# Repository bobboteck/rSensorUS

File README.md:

rSensorUS
=========

rSensorUS is a board for control up to 8 HC-SR04 Ultrasonic ranging modules based on Microchip PIC 18F2620.

The board have two analog input and one I2C master port, theoretically will be used to connect a temperature and humidity sensors, with the purpose of compensate the measurements of the ultrasonic sensors.

the communication with master controller can take place via serial TTL or RS-485.

The power voltage is 5 Volt.

Software develop used
======================
Currently the electric schema and the PCB was designed with Eagle 6.4 version, by CADSoft

For the code currently used MPLAB X version 1.90 and XC8 version 1.20, by Microchip

Now
====
Actualy working on Branch "Communication" to implement the Serial communication and protocol to mange the message and command received from Master

More info
==========
You can see more info on project in the wiki section

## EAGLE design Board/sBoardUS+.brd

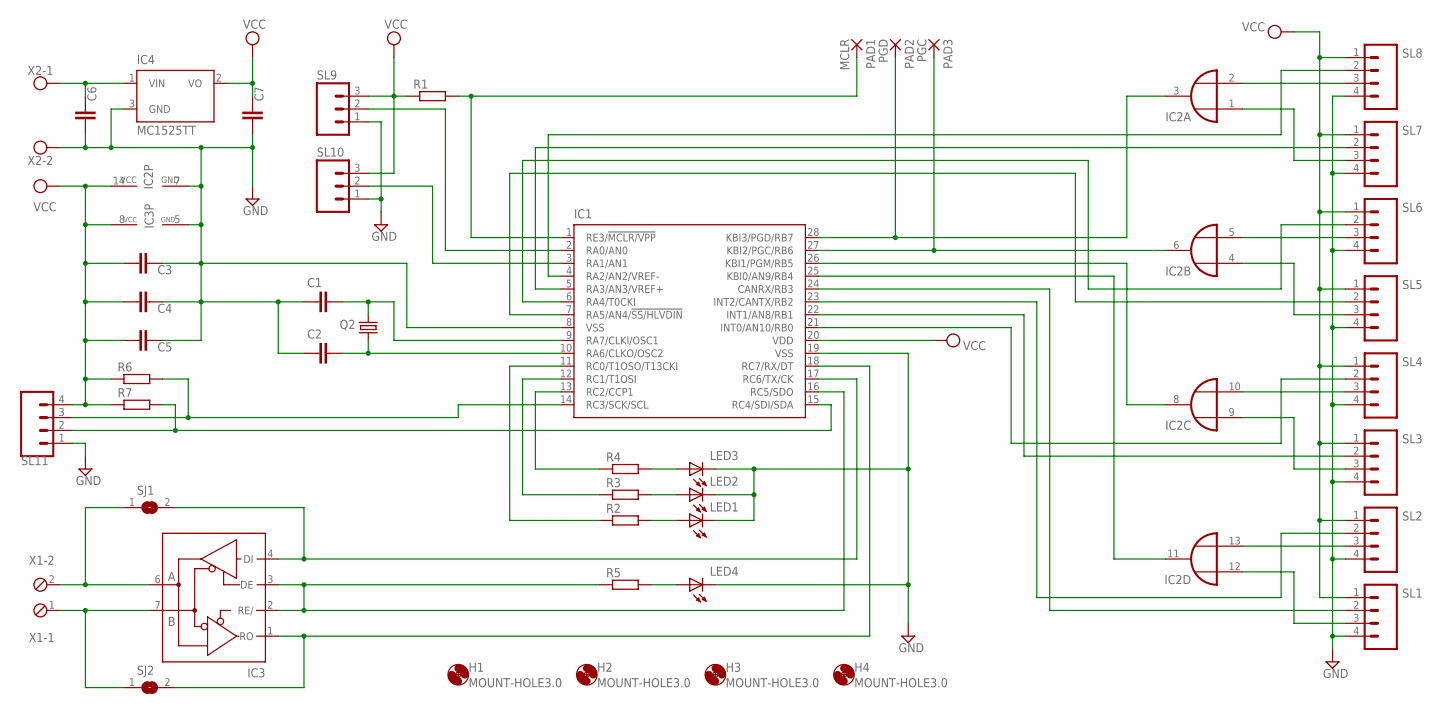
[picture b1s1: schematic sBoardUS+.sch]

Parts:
C1, C2, C3, C4, C5, C6, C7: C-EUC0805; C0805
H1, H2, H3, H4: MOUNT-HOLE3.0; 3,0
IC1: PIC18F2580-E/SO; SO28W
IC2: 74AC32D; SO14
IC3: MAX481CSA; SO08
IC4: MC1525TT; SOT23
LED1, LED2, LED3, LED4: LED; SMARTLED-TTW
PAD1: MCLR; SMD1,27-2,54
PAD2: PGD; SMD1,27-2,54
PAD3: PGC; SMD1,27-2,54
Q2: CRYSTALHC49U-V; HC49U-V
R1, R2, R3, R4, R5, R6, R7: R-EU_R0805; R0805
SJ1, SJ2: SJ
SL1, SL2, SL3, SL4, SL5, SL6, SL7, SL8, SL11: M04; 04P
SL9, SL10: M03; 03P
X1: MPT2; 2POL254
X2: AK500/2

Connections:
GND: C1.1, C2.1, C3.1, C4.1, C5.1, C6.2, C7.2, IC1.8 (VSS), IC1.19 (VSS), IC2.7 (GND), IC3.5 (GND), IC4.3 (GND), LED1.C@1 (C), LED2.C@1 (C), LED3.C@1 (C), LED4.C@1 (C), SL1.4, SL2.4, SL3.4, SL4.4, SL5.4, SL6.4, SL7.4, SL8.4, SL9.1, SL10.1, SL11.1, X2.2
unnamed: C1.2, IC1.9 (RA7/CLKI/OSC1), Q2.2
unnamed: C2.2, IC1.10 (RA6/CLKO/OSC2), Q2.1
unnamed: IC2.2 (I1), SL8.3
unnamed: IC1.1 (RE3/!MCLR/VPP), PAD1.1, R1.2
unnamed: IC1.2 (RA0/AN0), SL9.2
unnamed: IC1.3 (RA1/AN1), SL10.2
unnamed: IC1.25 (KBI0/AN9/RB4), IC2.11 (O)
unnamed: IC1.26 (KBI1/PGM/RB5), IC2.8 (O)
unnamed: IC1.27 (KBI2/PGC/RB6), IC2.6 (O), PAD3.1
unnamed: IC1.28 (KBI3/PGD/RB7), IC2.3 (O), PAD2.1
unnamed: IC2.5 (I1), SL6.3
unnamed: IC2.10 (I1), SL4.3
unnamed: IC2.13 (I1), SL2.3
unnamed: IC2.1 (I0), SL7.3
unnamed: IC2.4 (I0), SL5.3
unnamed: IC2.9 (I0), SL3.3
unnamed: IC2.12 (I0), SL1.3
unnamed: IC1.22 (INT1/AN8/RB1), SL3.2
unnamed: IC1.5 (RA3/AN3/VREF+), SL7.2
unnamed: IC1.4 (RA2/AN2/VREF-), SL8.2
unnamed: IC1.6 (RA4/T0CKI), SL6.2
unnamed: IC1.7 (RA5/AN4/!SS/HLVDIN), SL5.2
unnamed: IC1.21 (INT0/AN10/RB0), SL4.2
unnamed: IC1.24 (CANRX/RB3), SL1.2
unnamed: IC3.6 (A), SJ1.1, X1.2
unnamed: IC3.7 (B), SJ2.1, X1.1
unnamed: IC1.16 (RC5/SDO), IC3.2 (RE/), IC3.3 (DE), R5.1
unnamed: IC1.17 (RC6/TX/CK), IC3.4 (DI), SJ1.2
unnamed: IC1.18 (RC7/RX/DT), IC3.1 (RO), SJ2.2
unnamed: IC1.23 (INT2/CANTX/RB2), SL2.2
unnamed: IC1.11 (RC0/T1OSO/T13CKI), R2.1
unnamed: IC1.12 (RC1/T1OSI), R3.1
unnamed: IC1.13 (RC2/CCP1), R4.1
unnamed: LED3.A@1 (A), R4.2
unnamed: LED2.A@1 (A), R3.2
unnamed: LED1.A@1 (A), R2.2
unnamed: C6.1, IC4.1 (VIN), X2.1
unnamed: LED4.A@1 (A), R5.2
unnamed: IC1.14 (RC3/SCK/SCL), R6.2, SL11.3
unnamed: IC1.15 (RC4/SDI/SDA), R7.2, SL11.2
VCC: C3.2, C4.2, C5.2, C7.1, IC1.20 (VDD), IC2.14 (VCC), IC3.8 (VCC), IC4.2 (VO), R1.1, R6.1, R7.1, SL1.1, SL2.1, SL3.1, SL4.1, SL5.1, SL6.1, SL7.1, SL8.1, SL9.3, SL10.3, SL11.4

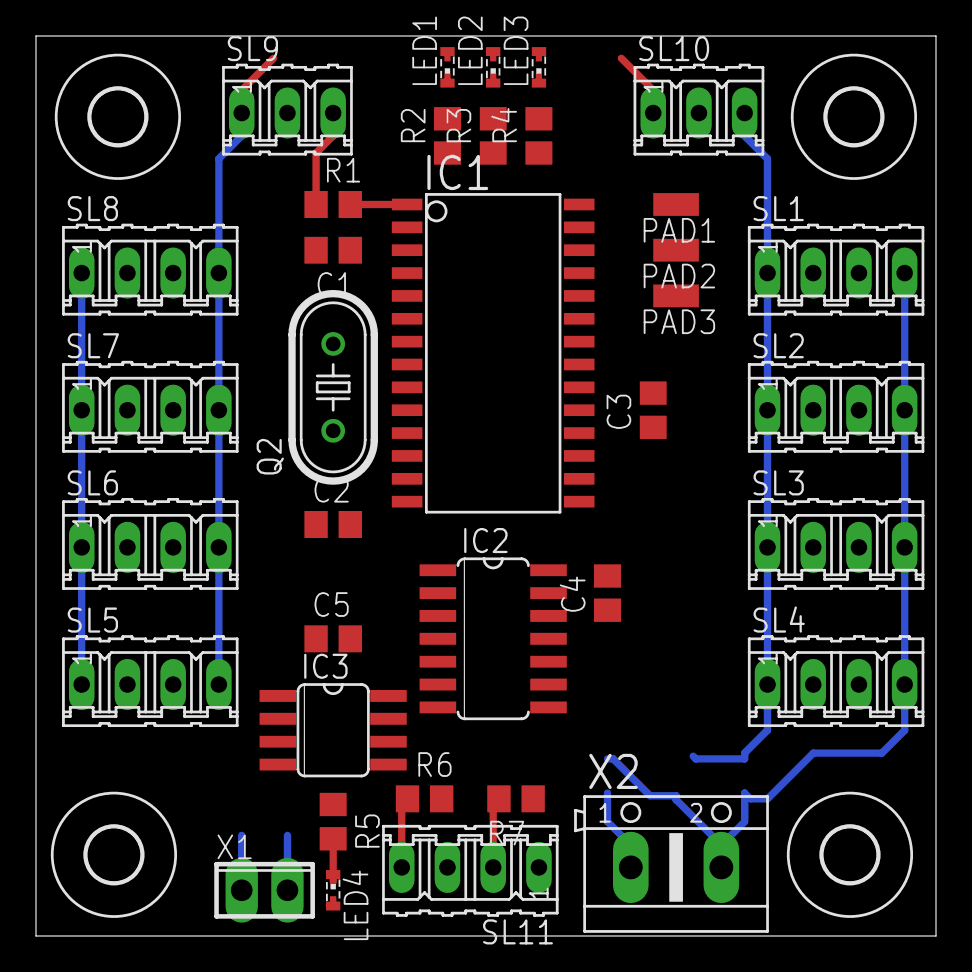
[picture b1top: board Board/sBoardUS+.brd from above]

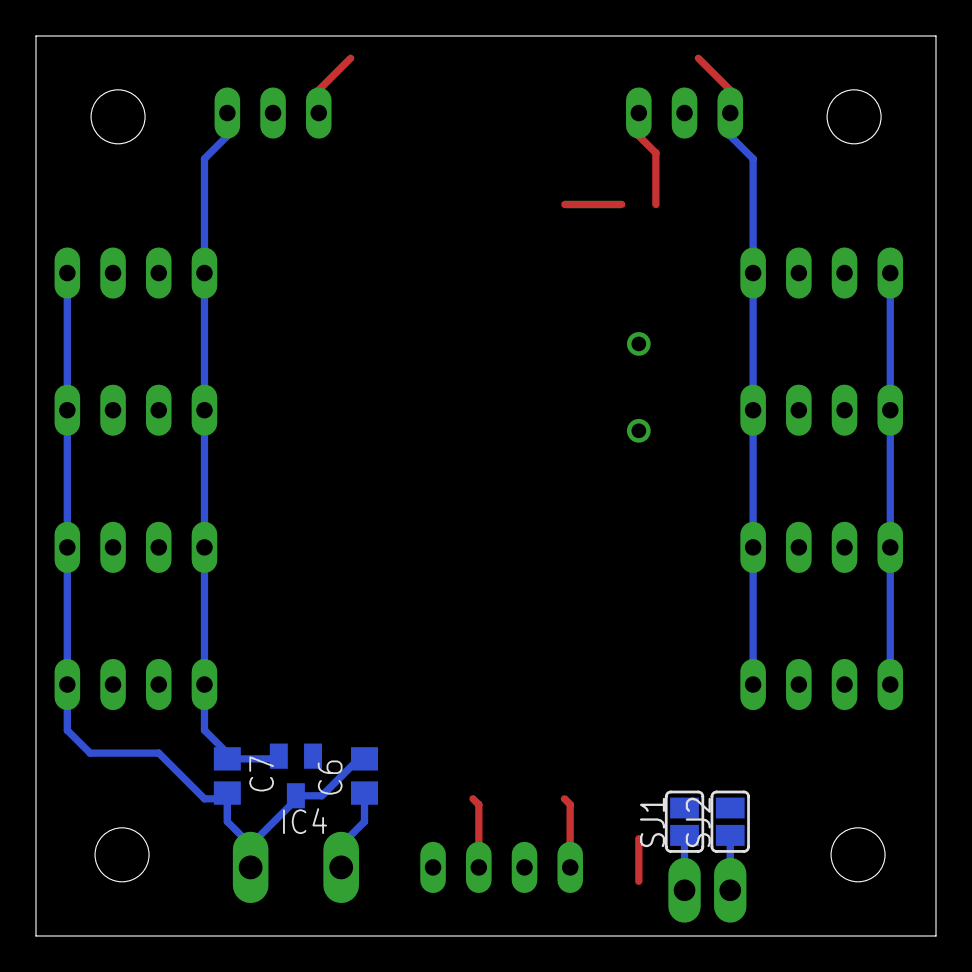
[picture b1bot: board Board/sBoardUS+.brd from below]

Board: 2 copper layers, 50.0 x 50.0 mm, 45 parts (5 on the bottom side), 42 nets.

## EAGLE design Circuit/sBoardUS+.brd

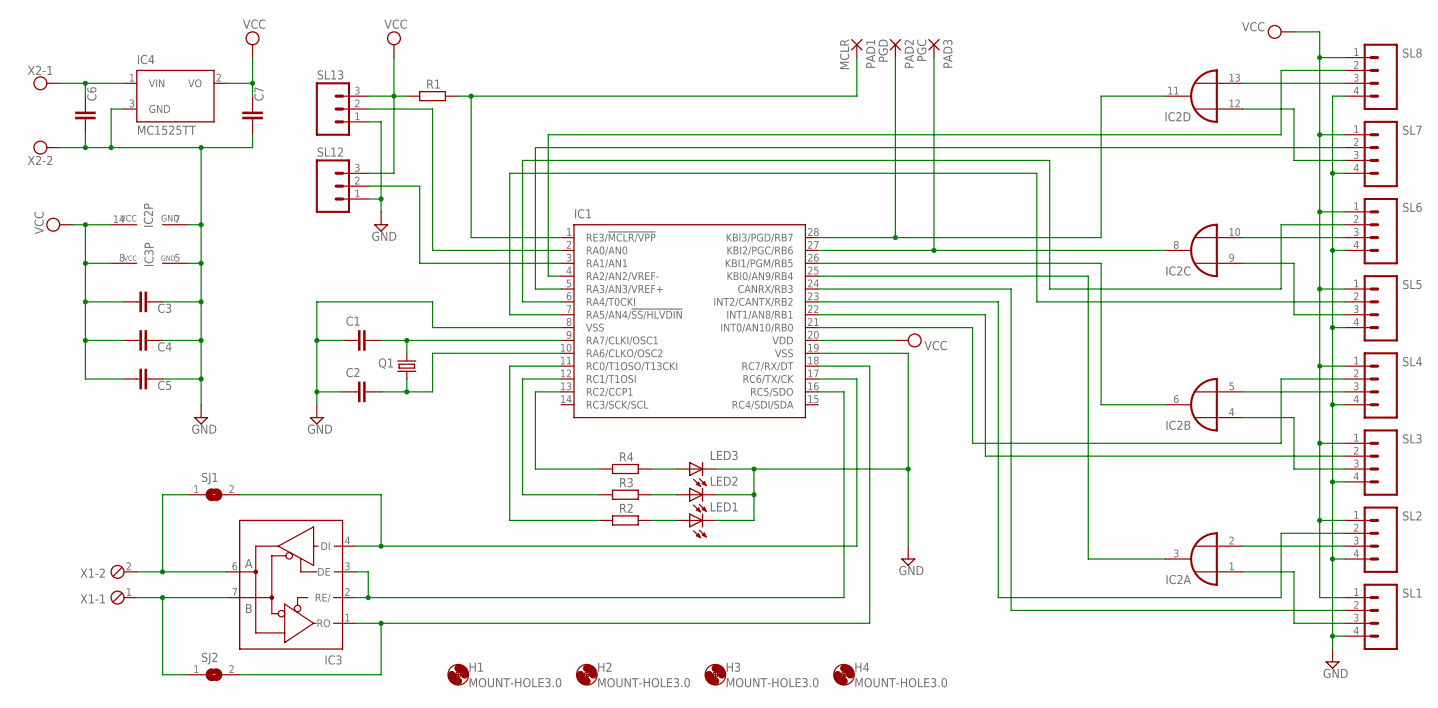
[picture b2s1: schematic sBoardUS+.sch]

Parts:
C1, C2, C3, C4, C5, C6, C7: C-EUC0805; C0805
H1, H2, H3, H4: MOUNT-HOLE3.0; 3,0
IC1: PIC18F2580-E/SO; SO28W
IC2: 74AC32D; SO14
IC3: MAX481CSA; SO08
IC4: MC1525TT; SOT23
LED1, LED2, LED3: LED; SMARTLED-TTW
PAD1: MCLR; SMD1,27-2,54
PAD2: PGD; SMD1,27-2,54
PAD3: PGC; SMD1,27-2,54
Q1: CRYSTALHC49UP; HC49UP
R1, R2, R3, R4: R-EU_M2012; M2012
SJ1, SJ2: SJ
SL1, SL2, SL3, SL4, SL5, SL6, SL7, SL8: M04; 04P
SL12, SL13: M03; 03P
X1: MPT2; 2POL254
X2: AK500/2

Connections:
GND: C1.1, C2.1, C3.1, C4.1, C5.1, C6.2, C7.2, IC1.8 (VSS), IC1.19 (VSS), IC2.7 (GND), IC3.5 (GND), IC4.3 (GND), LED1.C@1 (C), LED2.C@1 (C), LED3.C@1 (C), SL1.4, SL2.4, SL3.4, SL4.4, SL5.4, SL6.4, SL7.4, SL8.4, SL12.1, SL13.1, X2.2
unnamed: C1.2, IC1.9 (RA7/CLKI/OSC1), Q1.2
unnamed: C2.2, IC1.10 (RA6/CLKO/OSC2), Q1.1
unnamed: IC2.5 (I1), SL4.3
unnamed: IC1.1 (RE3/!MCLR/VPP), PAD1.1, R1.1
unnamed: IC1.2 (RA0/AN0), SL13.2
unnamed: IC1.3 (RA1/AN1), SL12.2
unnamed: IC1.25 (KBI0/AN9/RB4), IC2.3 (O)
unnamed: IC1.26 (KBI1/PGM/RB5), IC2.6 (O)
unnamed: IC1.27 (KBI2/PGC/RB6), IC2.8 (O), PAD3.1
unnamed: IC1.28 (KBI3/PGD/RB7), IC2.11 (O), PAD2.1
unnamed: IC2.2 (I1), SL2.3
unnamed: IC2.13 (I1), SL8.3
unnamed: IC2.10 (I1), SL6.3
unnamed: IC2.12 (I0), SL7.3
unnamed: IC2.9 (I0), SL5.3
unnamed: IC2.4 (I0), SL3.3
unnamed: IC2.1 (I0), SL1.3
unnamed: IC1.22 (INT1/AN8/RB1), SL3.2
unnamed: IC1.5 (RA3/AN3/VREF+), SL7.2
unnamed: IC1.4 (RA2/AN2/VREF-), SL8.2
unnamed: IC1.6 (RA4/T0CKI), SL6.2
unnamed: IC1.7 (RA5/AN4/!SS/HLVDIN), SL5.2
unnamed: IC1.21 (INT0/AN10/RB0), SL4.2
unnamed: IC1.24 (CANRX/RB3), SL1.2
unnamed: IC3.6 (A), SJ1.1, X1.2
unnamed: IC3.7 (B), SJ2.1, X1.1
unnamed: IC1.16 (RC5/SDO), IC3.2 (RE/), IC3.3 (DE)
unnamed: IC1.17 (RC6/TX/CK), IC3.4 (DI), SJ1.2
unnamed: IC1.18 (RC7/RX/DT), IC3.1 (RO), SJ2.2
unnamed: IC1.23 (INT2/CANTX/RB2), SL2.2
unnamed: IC1.11 (RC0/T1OSO/T13CKI), R2.2
unnamed: IC1.12 (RC1/T1OSI), R3.2
unnamed: IC1.13 (RC2/CCP1), R4.2
unnamed: LED3.A@1 (A), R4.1
unnamed: LED2.A@1 (A), R3.1
unnamed: LED1.A@1 (A), R2.1
unnamed: C6.1, IC4.1 (VIN), X2.1
VCC: C3.2, C4.2, C5.2, C7.1, IC1.20 (VDD), IC2.14 (VCC), IC3.8 (VCC), IC4.2 (VO), R1.2, SL1.1, SL2.1, SL3.1, SL4.1, SL5.1, SL6.1, SL7.1, SL8.1, SL12.3, SL13.3

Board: 2 copper layers, 40 parts (3 on the bottom side), 39 nets, no tracks yet.

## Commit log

2013-08-26 Adding schema and board
    Firsth commit of this files
2013-08-26 Aggiunti i pad per la programmazione ICSP
2013-08-28 Aggiornamento struttura e modifiche
    Cambiata la cartella di lavoro e ricreato il file BRD, modificato lo
    schema aggiungendo il led di TX/RX, aggiunto il connettore I2C, cambiato
    il quarzo.
2013-08-28 test
2013-08-28 Approntata disposizione
    Disposizione non definitiva dei componenti, in particolare per quanto
    riguarda i due integrati più piccoli, per il resto dovrebbe essere in un
    configurazione ottimale.
2013-08-29 Disegnate alcune piste delle alimentazioni ...
    ... e riposizionati alcuni componenti per evitare intrecci di piste.
    Devo chiedere consiglio per quanto riguarda il posizionamento dei due IC
    secondari, trovare il regolatore definitivo e verificare i condenstatori
    sul regolatore.
    Va anche invertito l'utilizzo delle porte OR in questo modo le piste si
    intrecciano troppo.
2013-08-31 Invertite le porte OR per ridurre gli incroci delle piste
2013-09-04 Aggiunta cartella contenente il codice del progetto
2013-09-04 Test commit per verificare utenza utilizzata su Github
2013-09-05 Aggiornato il file gitignore
    Per escludere file che prevedono impostazioni locali per il progetto
    MPLAB X, ho verificato che in questi cambiano i path tra windows e linux
2013-09-09 Aggiunta liberiria di Settings
2013-09-10 Aggiunti i file per la gestione della comunicazione
    Composta da tre strati, Serial gestisce la periferica, Protocol elabora
    i pacchetti ricevuti e da inviare, Parser analizza i dati ricevuti ed
    esegue le istruzioni necessarie per gestirli.
2013-09-11 Added SerialSettings function
    And relative calling
2013-09-26 Implementazione parziale della comunicazione
    Implementati i metodi di gestione seriale a basso livello tramite
    interrupt e la parte relativa al protocollo per l'interpretazione dei
    pacchetti.
    Ho fatto dei test con il simulatore, che mi ha permesso di sistemare
    diverse sviste. Mancano alcune cose come un buffer sulla ricezione e la
    gestione del pacchetto in caso di eventuali errori a basso livello.
2013-11-02 Aggiunta funzione per parsing comandi
    Al momento la funzione contiene solo codice per accendere e spengere due
    led, per eseguire un primo test di comunicazione
